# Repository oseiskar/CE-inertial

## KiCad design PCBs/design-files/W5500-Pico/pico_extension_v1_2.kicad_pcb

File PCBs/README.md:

# Inertial Module PCBs

NOTE: designs have not been proven to work and should be checked before ordering prototypes. 

Design files and libraries required for two Raspberry Pico implementations.

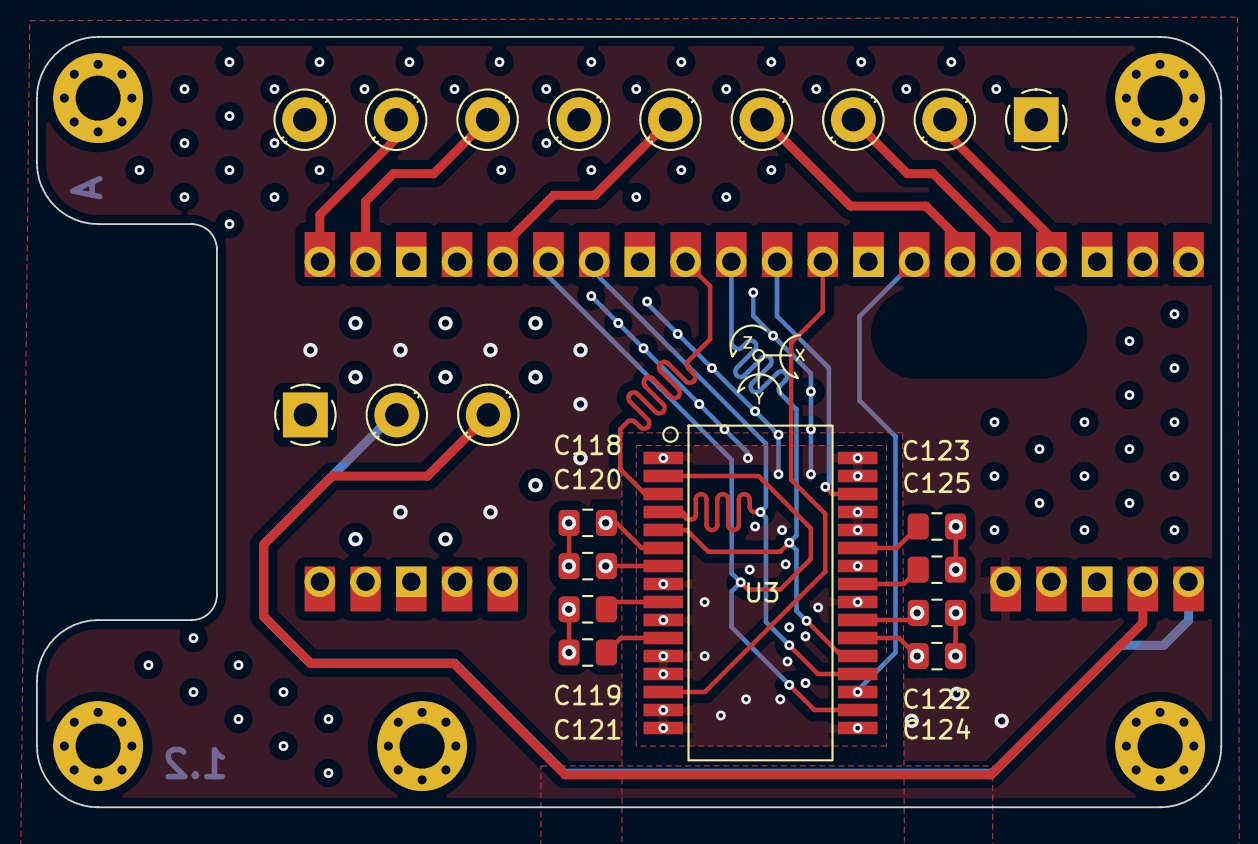
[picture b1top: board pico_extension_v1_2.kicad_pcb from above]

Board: 4 copper layers, 65.8 x 42.8 mm, 17 parts (0 on the bottom side), 21 nets.

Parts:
C118, C119, C121, C122, C123, C125: 1uF; C_0805_2012Metric_Pad1.18x1.45mm_HandSolder
C120, C124: 100nF; C_0805_2012Metric_Pad1.18x1.45mm_HandSolder
H1, H2, H3, H4, H5: MountingHole_Pad; MountingHole_2.5mm_Pad_Via
J1: Screw_Terminal_01x09; TerminalBlock_RND_205-00294_1x09_P5.08mm_Horizontal
J3: Screw_Terminal_01x03; TerminalBlock_RND_205-00288_1x03_P5.08mm_Horizontal
U1: PicoWiznetEVB; pico-w5500-evb-limited_pins
U3: SCHA63X; murata_scha

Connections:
3V3: C118.1, C120.1, C122.1, C124.1, U1.36 (3V3), U3.6 (DUE_V3p3D), U3.7 (DUE_V3p3A), U3.22 (UNO_V3p3D), U3.23 (UNO_V3p3A)
/EXT_DUE: U1.10 (GPIO7), U3.30 (DUE_TI/EXTERN)
/EXT_UNO: U1.9 (GPIO6), U3.14 (UNO_TI/EXTERN)
/SPI1_CS0: U1.12 (GPIO9), U3.3 (DUE_CSB)
/SPI1_CS1: U1.7 (GPIO5), U3.19 (UNO_CSB)
/SPI1_MISO: U1.11 (GPIO8), U3.5 (DUE_MISO), U3.21 (UNO_MISO)
/SPI1_MOSI: U1.15 (GPIO11), U3.2 (DUE_MOSI), U3.18 (UNO_MOSI)
/SPI1_SCK: U1.14 (GPIO10), U3.4 (DUE_SCK), U3.20 (UNO_SCK)
/TIME_IN: J1.8, U1.20 (GPIO15)
/TIME_OUT: J1.7, U1.19 (GPIO14)
/TRIG0: J1.2, U1.4 (GPIO2)
/TRIG1: J1.3, U1.5 (GPIO3)
/TRIG2: J1.4, U1.6 (GPIO4)
/TRIG3: J1.5, U1.16 (GPIO12)
/VBUS: J3.2, U1.40 (VBUS)
/VSYS: J3.3, U1.39 (VSYS)
GND: C118.2, C119.1, C120.2, C121.1, C122.2, C123.2, C124.2, C125.2, H1.1, H2.1, H3.1, H4.1, H5.1, J1.1, J1.6, J1.9, J3.1, U1.3 (GND), U1.8 (GND), U1.13 (GND), U1.18 (GND), U1.23 (GND), U1.38 (GND), U3.1 (EMC_GND), U3.8 (DUE_GNDD), U3.10 (UNO_GNDA/EMC_GND), U3.12 (RESERVED), U3.13 (UNO_TIOP), U3.15 (UNO_TION), U3.16 (EMC_GND), U3.17 (EMC_GND), U3.24 (UNO_GNDD), U3.26 (DUE_GNDA/EMC_GND), U3.28 (DUE_RESERVED), U3.29 (DUE_TIOP), U3.31 (DUE_TION), U3.32 (EMC_GND)
unnamed: C119.2, U3.9 (DUE_VDDD)
unnamed: C121.2, U3.11 (UNO_VDDA)
unnamed: C123.1, U3.27 (DUE_VDDA)
unnamed: C125.1, U3.25 (UNO_VDDD)

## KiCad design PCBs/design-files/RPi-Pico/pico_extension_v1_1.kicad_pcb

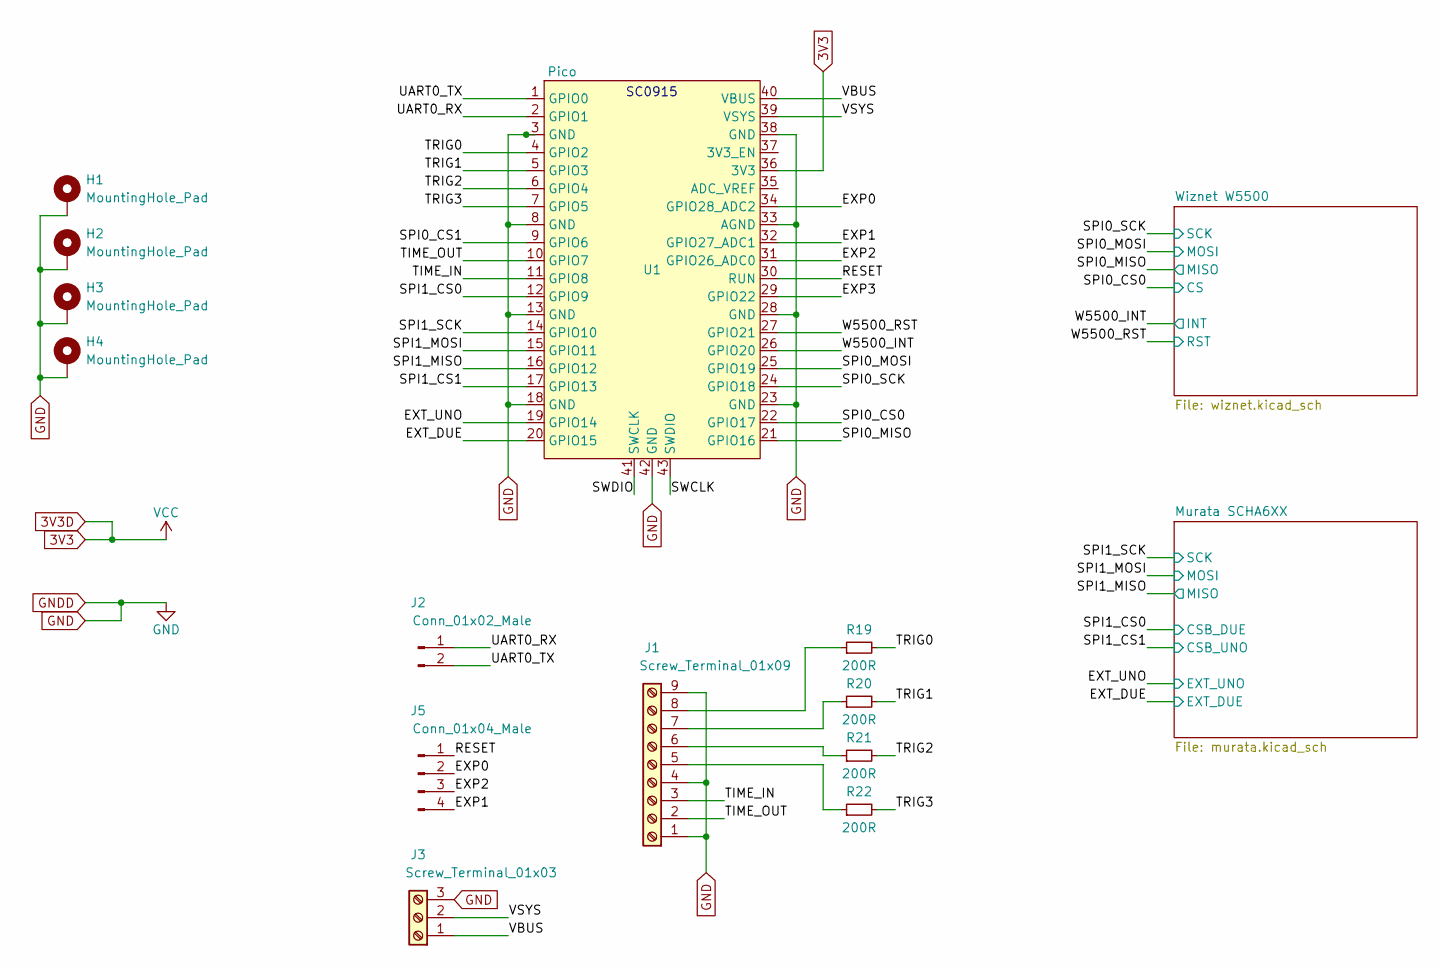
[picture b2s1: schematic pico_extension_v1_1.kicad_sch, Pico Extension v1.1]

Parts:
H1, H2, H3, H4: MountingHole_Pad; MountingHole_2.5mm_Pad_Via
J1: Screw_Terminal_01x09; TerminalBlock_RND_205-00294_1x09_P5.08mm_Horizontal
J2: Conn_01x02_Male; PinHeader_1x02_P2.54mm_Vertical
J3: Screw_Terminal_01x03; TerminalBlock_RND_205-00288_1x03_P5.08mm_Horizontal
J5: Conn_01x04_Male; PinHeader_2x02_P2.54mm_Vertical
R19, R20, R21, R22: 200R; R_0402_1005Metric; LCSC C25087
U1: Pico; RPi_Pico_SMD_nopins

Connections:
3V3: U1.36 (3V3); also elsewhere on the board
/EXP0: J5.2, U1.34 (GPIO28_ADC2)
/EXP1: J5.4, U1.32 (GPIO27_ADC1)
/EXP2: J5.3, U1.31 (GPIO26_ADC0)
/EXP3: U1.29 (GPIO22)
/EXT_DUE: U1.20 (GPIO15); also elsewhere on the board
/EXT_UNO: U1.19 (GPIO14); also elsewhere on the board
/RESET: J5.1, U1.30 (RUN)
/SPI0_CS0: U1.22 (GPIO17); also elsewhere on the board
/SPI0_CS1: U1.9 (GPIO6)
/SPI0_MISO: U1.21 (GPIO16); also elsewhere on the board
/SPI0_MOSI: U1.25 (GPIO19); also elsewhere on the board
/SPI0_SCK: U1.24 (GPIO18); also elsewhere on the board
/SPI1_CS0: U1.12 (GPIO9); also elsewhere on the board
/SPI1_CS1: U1.17 (GPIO13); also elsewhere on the board
/SPI1_MISO: U1.16 (GPIO12); also elsewhere on the board
/SPI1_MOSI: U1.15 (GPIO11); also elsewhere on the board
/SPI1_SCK: U1.14 (GPIO10); also elsewhere on the board
/SWCLK: U1.43 (SWDIO)
/SWDIO: U1.41 (SWCLK)
/TIME_IN: J1.3, U1.11 (GPIO8)
/TIME_OUT: J1.2, U1.10 (GPIO7)
/TRIG0: R19.2, U1.4 (GPIO2)
/TRIG1: R20.2, U1.5 (GPIO3)
/TRIG2: R21.2, U1.6 (GPIO4)
/TRIG3: R22.2, U1.7 (GPIO5)
/UART0_RX: J2.1, U1.2 (GPIO1)
/UART0_TX: J2.2, U1.1 (GPIO0)
/VBUS: J3.1, U1.40 (VBUS)
/VSYS: J3.2, U1.39 (VSYS)
/W5500_INT: U1.26 (GPIO20); also elsewhere on the board
/W5500_RST: U1.27 (GPIO21); also elsewhere on the board
GND: H1.1, H2.1, H3.1, H4.1, J1.1, J1.4, J1.9, J3.3, U1.3 (GND), U1.8 (GND), U1.13 (GND), U1.18 (GND), U1.23 (GND), U1.28 (GND), U1.33 (AGND), U1.38 (GND), U1.42 (GND); also elsewhere on the board
unnamed: J1.5, R22.1
unnamed: J1.6, R21.1
unnamed: J1.7, R20.1
unnamed: J1.8, R19.1

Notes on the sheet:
SC0915

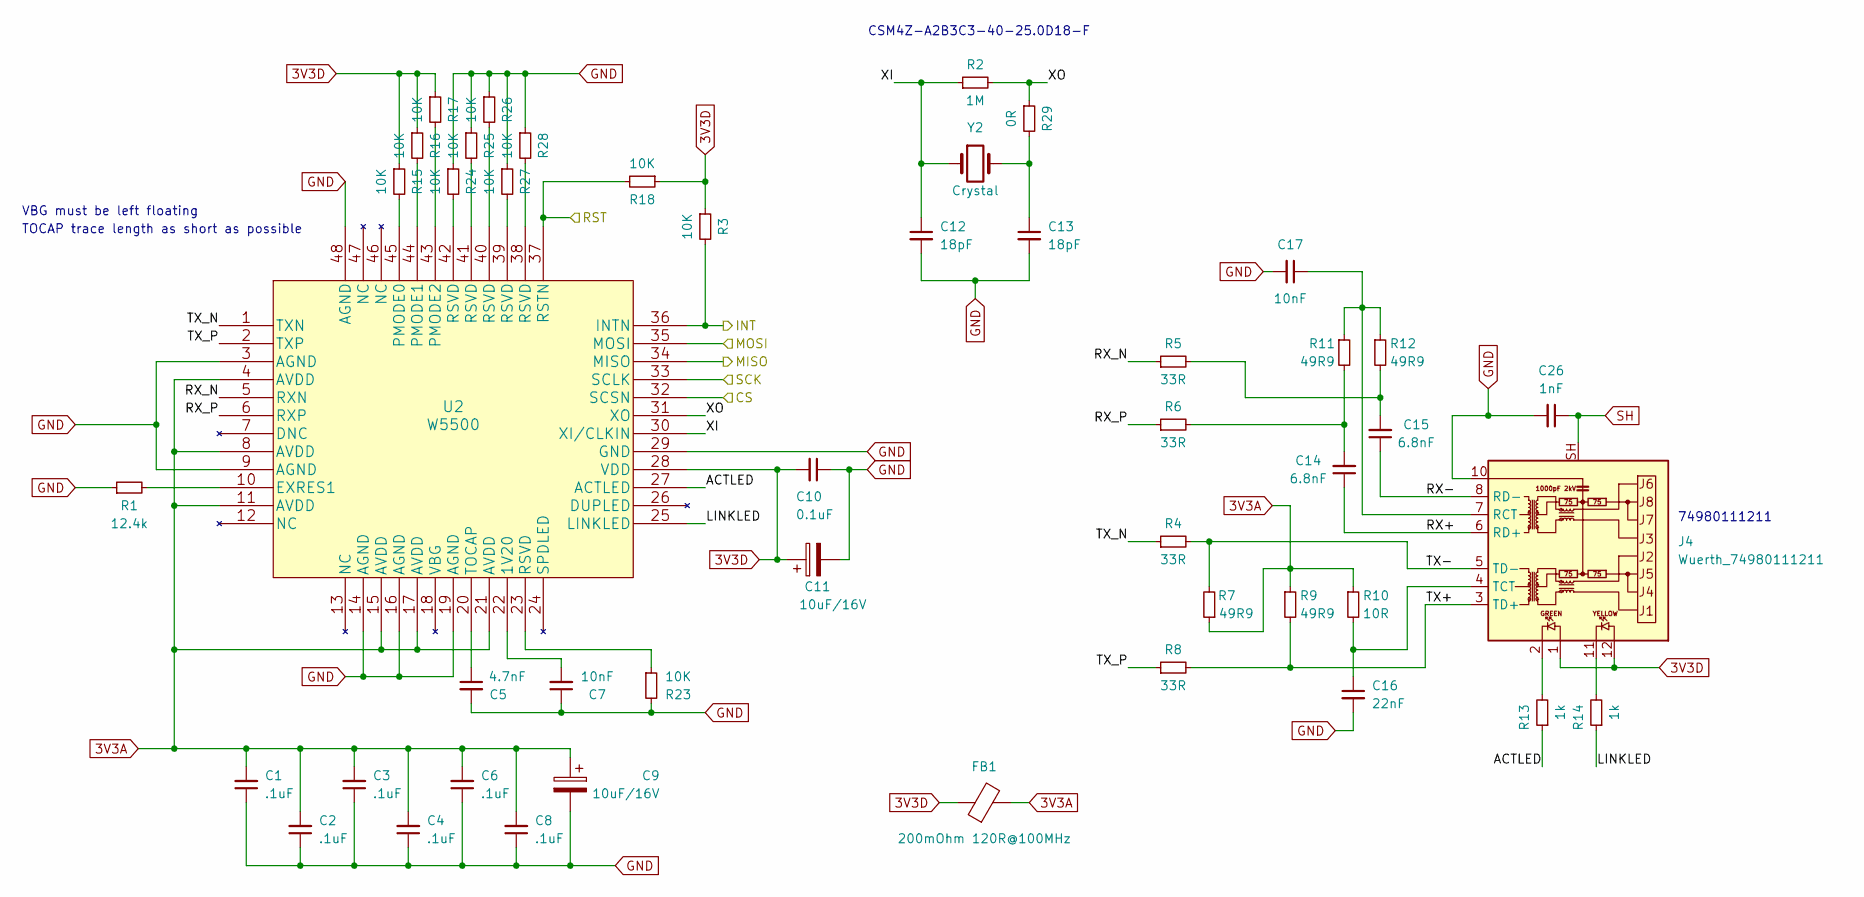
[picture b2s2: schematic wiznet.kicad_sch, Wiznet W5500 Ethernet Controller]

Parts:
C1, C2, C3, C4, C6, C8: .1uF; C_0402_1005Metric; LCSC C1546
C5: 4.7nF; C_0402_1005Metric; LCSC C1538
C7, C17: 10nF; C_0402_1005Metric; LCSC C15195
C9, C11: 10uF/16V; C_0402_1005Metric; LCSC C15525
C10: 0.1uF; C_0402_1005Metric; LCSC C1546
C12, C13: 18pF; C_0402_1005Metric; LCSC C1549
C14, C15: 6.8nF; C_0402_1005Metric; LCSC C1576
C16: 22nF; C_0402_1005Metric; LCSC C1532
C26: 1nF; C_0402_1005Metric; LCSC C1523
FB1: 200mOhm 120R@100MHz; L_1206_3216Metric_Pad1.22x1.90mm_HandSolder; LCSC C85841
J4: Wuerth_74980111211; RJ45_Wuerth_74980111211_h
R1: 12.4k; R_0402_1005Metric; LCSC C325375
R2: 1M; R_0402_1005Metric; LCSC C26083
R3, R15, R16, R17, R18, R23, R24, R25, R26, R27, R28: 10K; R_0402_1005Metric; LCSC C25744
R4, R5, R6, R8: 33R; R_0402_1005Metric; LCSC C138002
R7, R9, R11, R12: 49R9; R_0402_1005Metric; LCSC C144754
R10: 10R; R_0402_1005Metric; LCSC C176108
R13, R14: 1k; R_0402_1005Metric; LCSC C11702
R29: 0R; R_0603_1608Metric; LCSC C21189
U2: W5500; w5500; LCSC C32843
Y2: Crystal; Crystal_SMD_HC49-SD; LCSC C390751

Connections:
3V3: C10.2, C11.1, FB1.1, J4.1, J4.12, R3.1, R15.1, R16.1, R17.1, R18.1, U2.28 (VDD); also elsewhere on the board
3V3A: C1.2, C2.2, C3.2, C4.2, C6.2, C8.2, C9.1, FB1.2, R7.1, R9.1, R10.1, U2.4 (AVDD), U2.8 (AVDD), U2.11 (AVDD), U2.15 (AVDD), U2.17 (AVDD), U2.21 (AVDD)
/SPI0_CS0: U2.32 (SCSN); also elsewhere on the board
/SPI0_MISO: U2.34 (MISO); also elsewhere on the board
/SPI0_MOSI: U2.35 (MOSI); also elsewhere on the board
/SPI0_SCK: U2.33 (SCLK); also elsewhere on the board
/W5500_INT: R3.2, U2.36 (INTN); also elsewhere on the board
/W5500_RST: R18.2, U2.37 (RSTN); also elsewhere on the board
/Wiznet W5500/ACTLED: R13.1, U2.27 (ACTLED)
/Wiznet W5500/LINKLED: R14.1, U2.25 (LINKLED)
/Wiznet W5500/RX+: C14.1, J4.6 (RD+)
/Wiznet W5500/RX-: C15.1, J4.8 (RD-)
/Wiznet W5500/RX_N: R5.1, U2.5 (RXN)
/Wiznet W5500/RX_P: R6.1, U2.6 (RXP)
/Wiznet W5500/TX+: J4.3 (TD+), R8.2, R9.2
/Wiznet W5500/TX-: J4.5 (TD-), R4.2, R7.2
/Wiznet W5500/TX_N: R4.1, U2.1 (TXN)
/Wiznet W5500/TX_P: R8.1, U2.2 (TXP)
/Wiznet W5500/XI: C12.1, R2.1, U2.30 (XI/CLKIN), Y2.1
/Wiznet W5500/XO: R2.2, R29.1, U2.31 (XO)
GND: C1.1, C2.1, C3.1, C4.1, C5.2, C6.1, C7.1, C8.1, C9.2, C10.1, C11.2, C12.2, C13.2, C16.2, C17.2, C26.2, J4.10, R1.1, R23.2, R24.1, R25.1, R26.1, R27.1, R28.1, U2.3 (AGND), U2.9 (AGND), U2.14 (AGND), U2.16 (AGND), U2.19 (AGND), U2.29 (GND), U2.48 (AGND); also elsewhere on the board
unnamed: C5.1, U2.20 (TOCAP)
unnamed: C7.2, U2.22 (1V20)
unnamed: C13.1, R29.2, Y2.2
unnamed: C14.2, R6.2, R11.2
unnamed: C15.2, R5.2, R12.2
unnamed: C16.1, J4.4 (TCT), R10.2
unnamed: C17.1, J4.7 (RCT), R11.1, R12.1
unnamed: J4.2, R13.2
unnamed: J4.11, R14.2
unnamed: R1.2, U2.10 (EXRES1)
unnamed: R15.2, U2.45 (PMODE0)
unnamed: R16.2, U2.44 (PMODE1)
unnamed: R17.2, U2.43 (PMODE2)
unnamed: R23.1, U2.23 (RSVD)
unnamed: R24.2, U2.42 (RSVD)
unnamed: R25.2, U2.41 (RSVD)
unnamed: R26.2, U2.40 (RSVD)
unnamed: R27.2, U2.39 (RSVD)
unnamed: R28.2, U2.38 (RSVD)
SH: C26.1, J4.SH

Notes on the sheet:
CSM4Z-A2B3C3-40-25.0D18-F
VBG must be left floating
TOCAP trace length as short as possible
74980111211

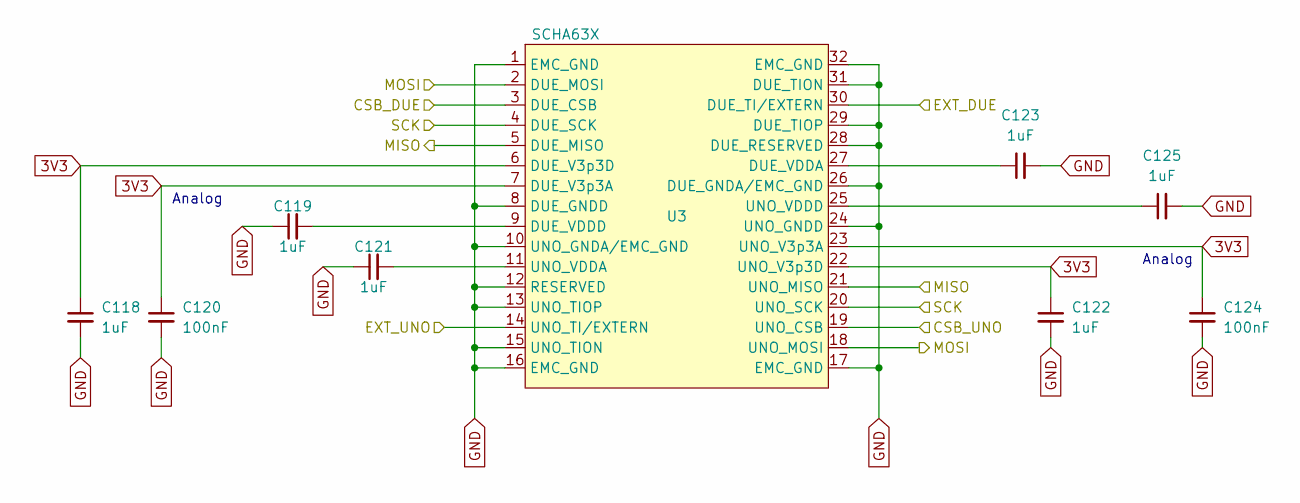
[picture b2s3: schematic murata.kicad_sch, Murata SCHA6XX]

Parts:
C118, C119, C121, C122, C123, C125: 1uF; C_0402_1005Metric; LCSC C52923
C120, C124: 100nF; C_0402_1005Metric; LCSC C1525
U3: SCHA63X; murata_scha

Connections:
3V3: C118.1, C120.1, C122.1, C124.1, U3.6 (DUE_V3p3D), U3.7 (DUE_V3p3A), U3.22 (UNO_V3p3D), U3.23 (UNO_V3p3A); also elsewhere on the board
/EXT_DUE: U3.30 (DUE_TI/EXTERN); also elsewhere on the board
/EXT_UNO: U3.14 (UNO_TI/EXTERN); also elsewhere on the board
/SPI1_CS0: U3.3 (DUE_CSB); also elsewhere on the board
/SPI1_CS1: U3.19 (UNO_CSB); also elsewhere on the board
/SPI1_MISO: U3.5 (DUE_MISO), U3.21 (UNO_MISO); also elsewhere on the board
/SPI1_MOSI: U3.2 (DUE_MOSI), U3.18 (UNO_MOSI); also elsewhere on the board
/SPI1_SCK: U3.4 (DUE_SCK), U3.20 (UNO_SCK); also elsewhere on the board
GND: C118.2, C119.1, C120.2, C121.1, C122.2, C123.2, C124.2, C125.2, U3.1 (EMC_GND), U3.8 (DUE_GNDD), U3.10 (UNO_GNDA/EMC_GND), U3.12 (RESERVED), U3.13 (UNO_TIOP), U3.15 (UNO_TION), U3.16 (EMC_GND), U3.17 (EMC_GND), U3.24 (UNO_GNDD), U3.26 (DUE_GNDA/EMC_GND), U3.28 (DUE_RESERVED), U3.29 (DUE_TIOP), U3.31 (DUE_TION), U3.32 (EMC_GND); also elsewhere on the board
unnamed: C119.2, U3.9 (DUE_VDDD)
unnamed: C121.2, U3.11 (UNO_VDDA)
unnamed: C123.1, U3.27 (DUE_VDDA)
unnamed: C125.1, U3.25 (UNO_VDDD)

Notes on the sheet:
Analog

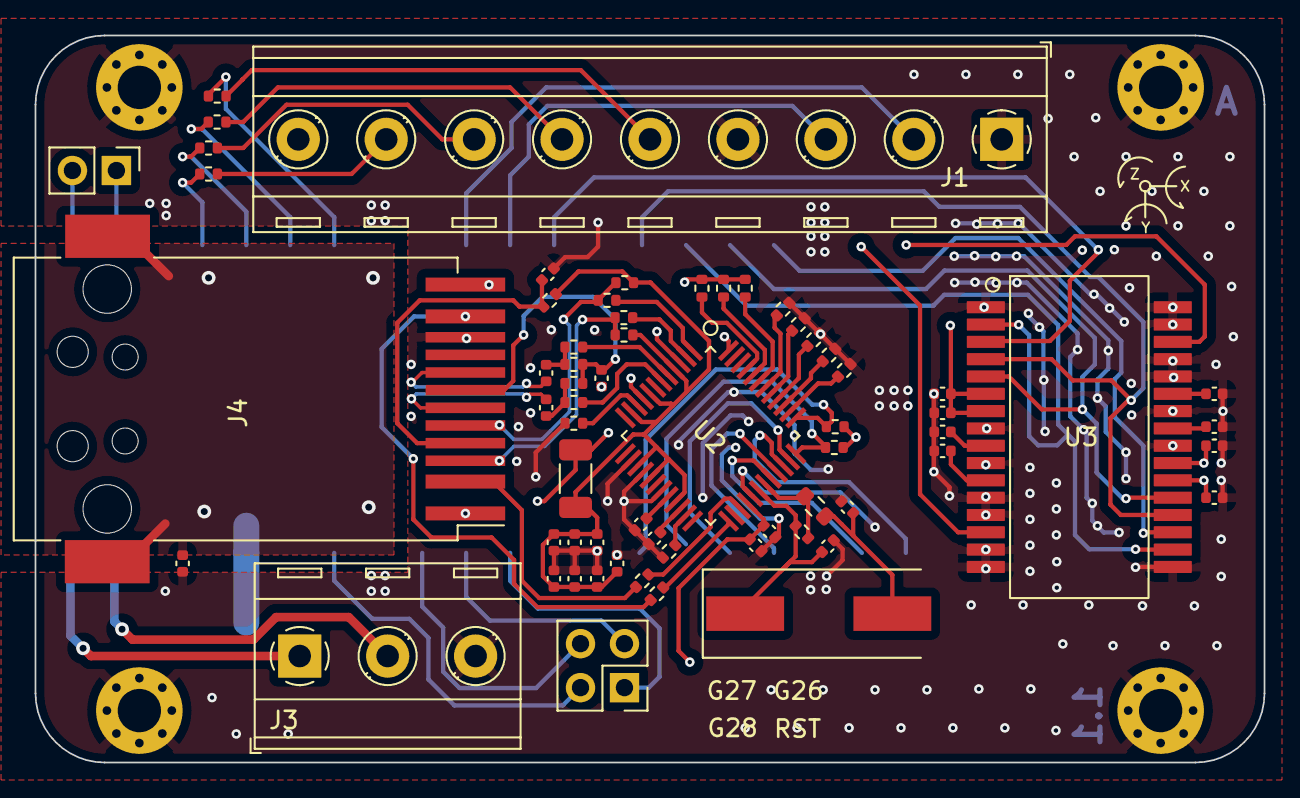
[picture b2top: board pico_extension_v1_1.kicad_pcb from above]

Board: 4 copper layers, 71.0 x 42.0 mm, 69 parts (1 on the bottom side), 70 nets.

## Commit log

2022-09-25 Add schematics
2022-10-12 Add (CMake) build dir to .gitignore
2022-10-12 Add test/ folder and CMakeFile
    Maybe needed due to a bad CMakeLists.txt somewhere else (pico-sdk?)
2022-10-12 Tune CMakeLists.txt and main.c
    * import pico SDK from ENV variable
    * remove unused url helper
    * remove unused/nonexistent 'test' folder
2022-10-12 Fix/change pin numbers in scha63x_spi.c and tune debug prints
2022-10-15 Various fixes

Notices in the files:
PCBs/design-files/RPi-Pico/pico_extension_v1_1.kicad_pcb:
© 2022 Christian Kaarre
